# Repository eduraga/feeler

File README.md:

# Feeler

## Installation

- Install MindsetProcessing http://jorgecardoso.eu/processing/MindSetProcessing/ in Processing.
- Install feelerSerial in Processing.

### Without PHP backend
- Change the first in feelerApp.pde line to ```boolean debug = true;```.
- The application now runs in 'debug' mode, so you can login by clicking 'L' on the keyboard.

### With PHP backend
- Install a PHP server, such as MAMP https://www.mamp.info/en/, and run it.
- Install the contents of /SimpleUsers (a modified version of: https://github.com/Repox/SimpleUsers and create a user).
  - Edit the configuration file, located at simpleusers/config.inc.php, then run the install script which is located at simpleusers/install.php As an alternative to the install script, edit the configuration file. The tables can be created manually, by opening tables.sql and pasting the tables into phpMyAdmin.
- Edit feelerApp/data/config.json to reflect your environment.

## Running
- Run feelerApp.pde (in /feelerSerial) and try to create a user or log in (or ref. to running without PHP).
- Set ```simulateMindSet``` to true to test without MindWave.
- Set ```simulateBoxes``` to true to test without the boxes.
- Change ```countDownStartMeditate``` and ```countDownStartStudy``` (in minutes, accepts fractions) to the appropriate values.

## License
Feeler is licensed under GPL3 license, see COPYING

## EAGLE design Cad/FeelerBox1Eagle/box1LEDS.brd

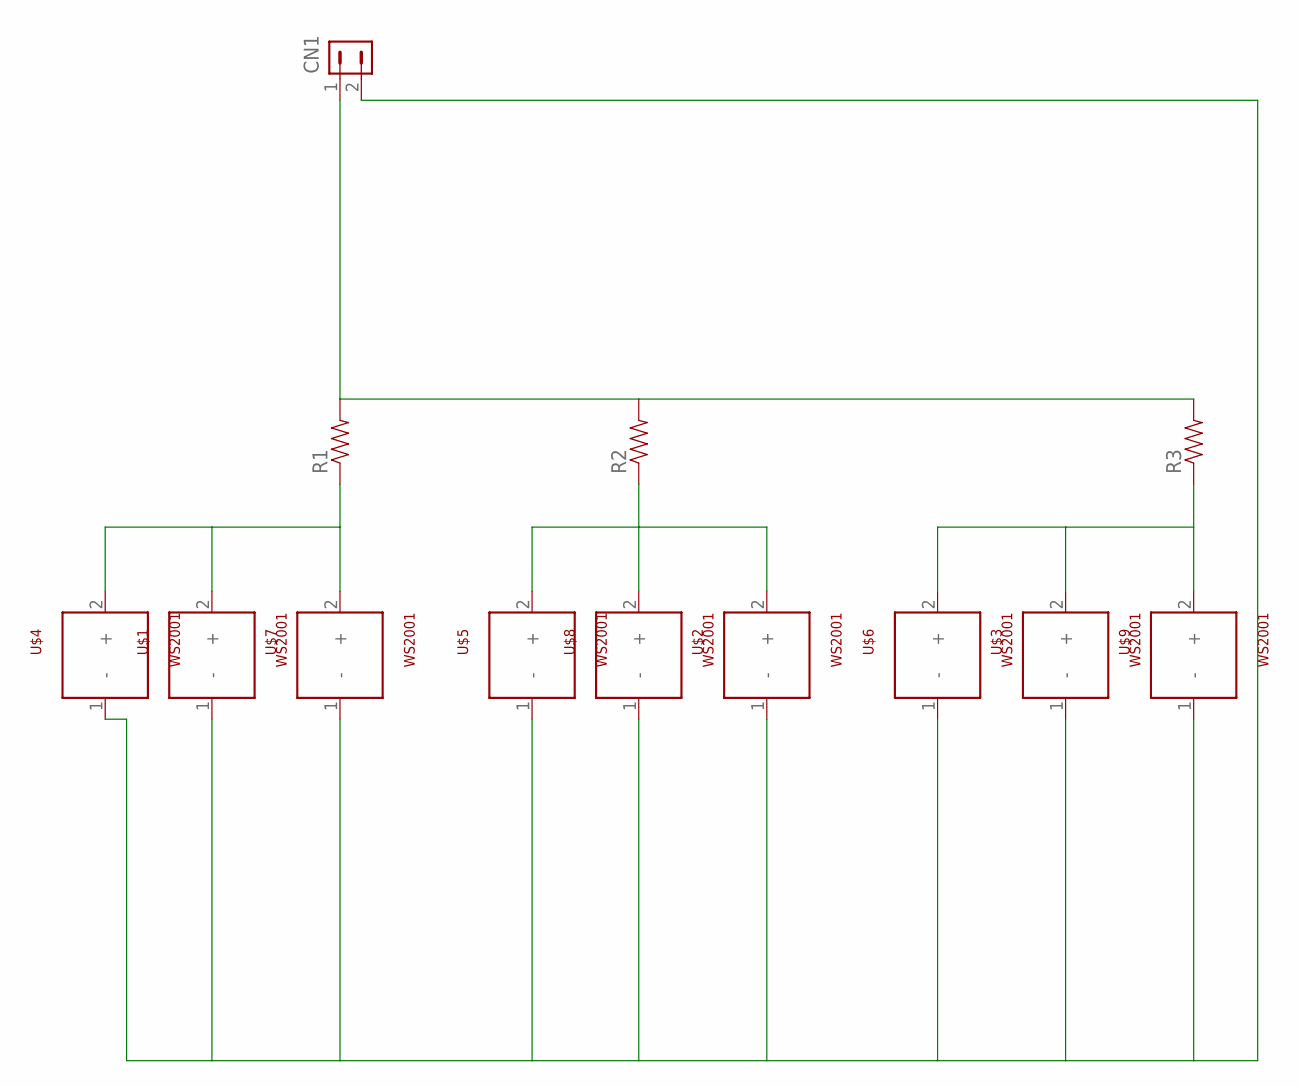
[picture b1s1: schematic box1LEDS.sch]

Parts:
CN1: HDR-1X2-SIP-100; SIP-100-2V
R1, R2, R3: RESISTORPTH-1/4W; AXIAL-0.4
U$1, U$2, U$3, U$4, U$5, U$6, U$7, U$8, U$9: WS2001; WH2001

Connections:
GND: CN1.2, U$1.1 (-), U$2.1 (-), U$3.1 (-), U$4.1 (-), U$5.1 (-), U$6.1 (-), U$7.1 (-), U$8.1 (-), U$9.1 (-)
unnamed: R3.P$1 (1), U$3.2 (+), U$6.2 (+), U$9.2 (+)
unnamed: R2.P$1 (1), U$2.2 (+), U$5.2 (+), U$8.2 (+)
unnamed: R1.P$1 (1), U$1.2 (+), U$4.2 (+), U$7.2 (+)
unnamed: CN1.1, R1.P$2 (2), R2.P$2 (2), R3.P$2 (2)

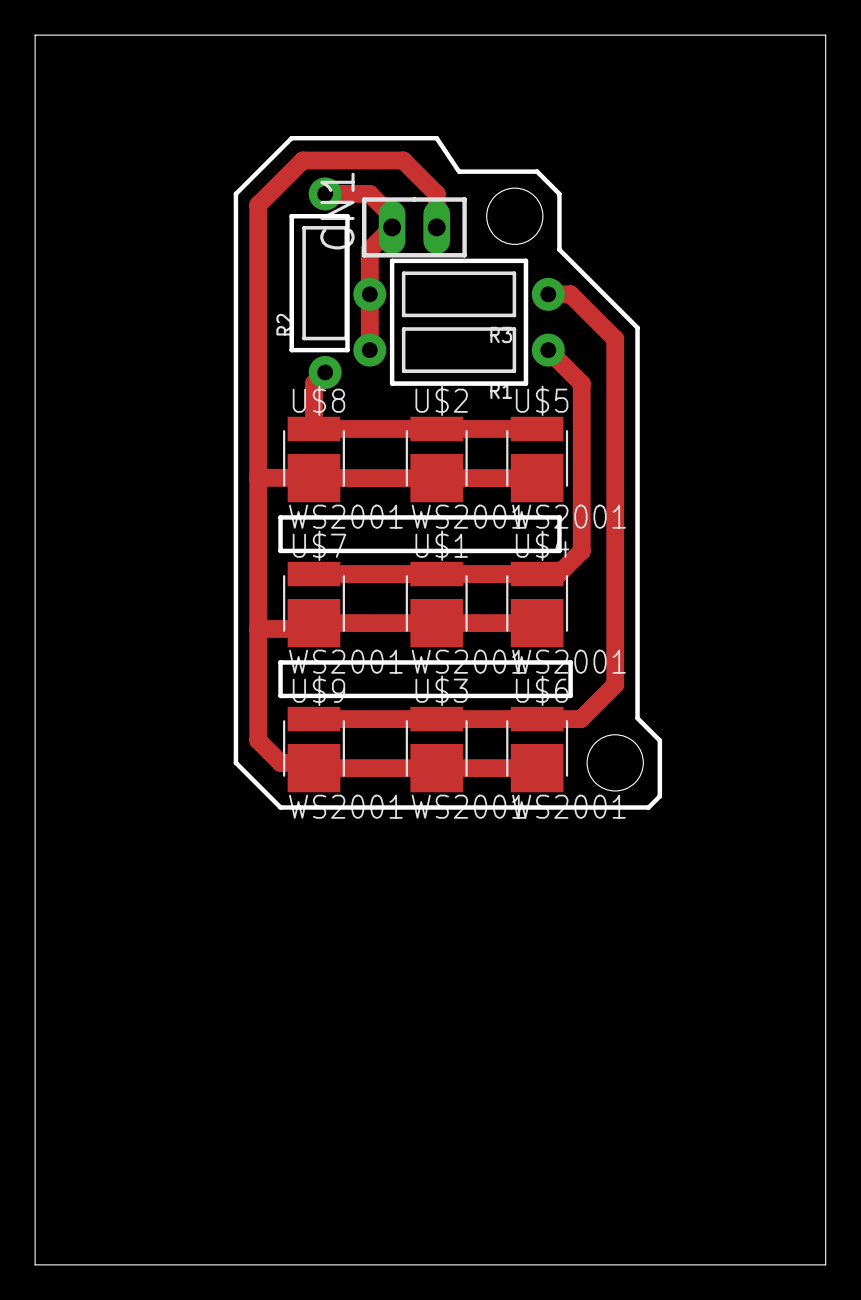
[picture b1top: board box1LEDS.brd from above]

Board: 2 copper layers, 44.7 x 69.7 mm, 13 parts (0 on the bottom side), 5 nets.

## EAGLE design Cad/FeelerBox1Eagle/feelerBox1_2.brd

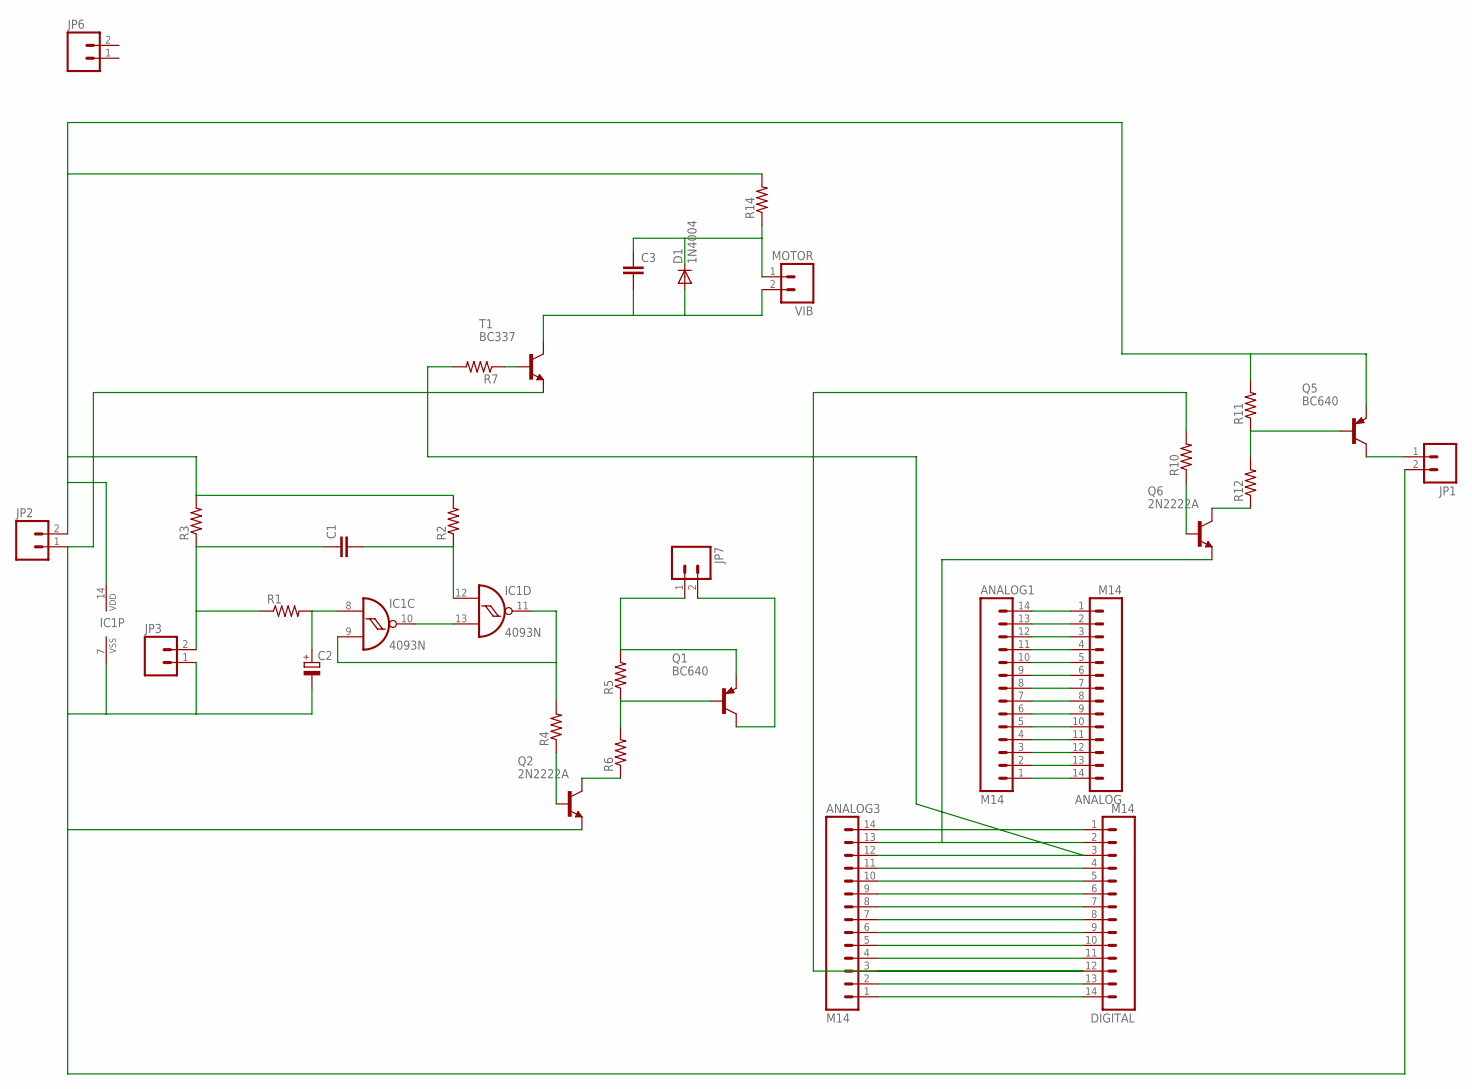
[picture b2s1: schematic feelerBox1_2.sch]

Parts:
ANALOG, ANALOG1, ANALOG3: M14; 1X14
C1: 0.1UF-50V-20%(PTH)KIT-EZ; CAP-PTH-SMALL-KIT
C2: CPOL-EUE2.5-5; E2,5-5
C3: CAPKIT; CAP-PTH-SMALL-KIT
D1: 1N4004; DO41-10
DIGITAL: M14; 1X14
IC1: 4093N; DIL14
JP1, JP2, JP3, JP6, JP7: M02PTH; 1X02
Q1, Q5: BC640; TO92-BCE
Q2, Q6: 2N2222A; TO18
R1, R2, R3, R7: RESISTORAXIAL-0.3; AXIAL-0.3
R4, R5, R6, R10, R11, R12, R14: RESISTORPTH-1/4W-VERT; AXIAL-0.1
T1: BC337; TO92
VIB: MOTOR; 1X02

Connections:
A1: IC1.9 (I1), IC1.11 (O), R4.P$2 (2)
A2: ANALOG.9, ANALOG1.6
A3: ANALOG.10, ANALOG1.5
A4: ANALOG.11, ANALOG1.4
A5: ANALOG.12, ANALOG1.3
A6: ANALOG.13, ANALOG1.2
A7: ANALOG.14, ANALOG1.1
A8: ANALOG3.4, DIGITAL.11
A9: ANALOG3.3, DIGITAL.12, R10.P$2 (2)
BATTERYGND: C2.-, IC1.7 (VSS), JP1.2, JP2.1, JP3.1, Q2.1 (E), T1.1 (E)
BATTERYPWR: IC1.14 (VDD), JP2.2, Q5.E, R2.P$2 (2), R3.P$2 (2), R11.P$2 (2), R14.P$2 (2)
D2: ANALOG3.12, DIGITAL.3, R7.P$2 (2)
D4: ANALOG3.10, DIGITAL.5
D6: ANALOG3.8, DIGITAL.7
D7: ANALOG3.7, DIGITAL.8
D8: ANALOG3.6, DIGITAL.9
D9: ANALOG3.5, DIGITAL.10
GND: ANALOG3.13, DIGITAL.2, Q6.1 (E)
GND2: ANALOG3.14, DIGITAL.1
unnamed: IC1.10 (O), IC1.13 (I1)
unnamed: Q1.B, R5.P$1 (1), R6.P$2 (2)
unnamed: C2.+, IC1.8 (I0), R1.P$2 (2)
unnamed: ANALOG.6, ANALOG1.9
unnamed: C1.1, JP3.2, R1.P$1 (1), R3.P$1 (1)
unnamed: C1.2, IC1.12 (I0), R2.P$1 (1)
unnamed: Q2.3 (C), R6.P$1 (1)
unnamed: JP7.2, Q1.C
unnamed: Q2.2 (B), R4.P$1 (1)
unnamed: JP7.1, Q1.E, R5.P$2 (2)
unnamed: ANALOG.1, ANALOG1.14
unnamed: ANALOG.2, ANALOG1.13
unnamed: ANALOG.3, ANALOG1.12
unnamed: ANALOG.4, ANALOG1.11
unnamed: ANALOG.5, ANALOG1.10
unnamed: R7.P$1 (1), T1.2 (B)
unnamed: ANALOG.7, ANALOG1.8
unnamed: ANALOG.8, ANALOG1.7
unnamed: Q5.B, R11.P$1 (1), R12.P$2 (2)
unnamed: ANALOG3.1, DIGITAL.14
unnamed: ANALOG3.2, DIGITAL.13
unnamed: ANALOG3.9, DIGITAL.6
unnamed: ANALOG3.11, DIGITAL.4
unnamed: Q6.3 (C), R12.P$1 (1)
unnamed: C3.2, D1.A, T1.3 (C), VIB.2
unnamed: C3.1, D1.C, R14.P$1 (1), VIB.1
unnamed: Q6.2 (B), R10.P$1 (1)
unnamed: JP1.1, Q5.C

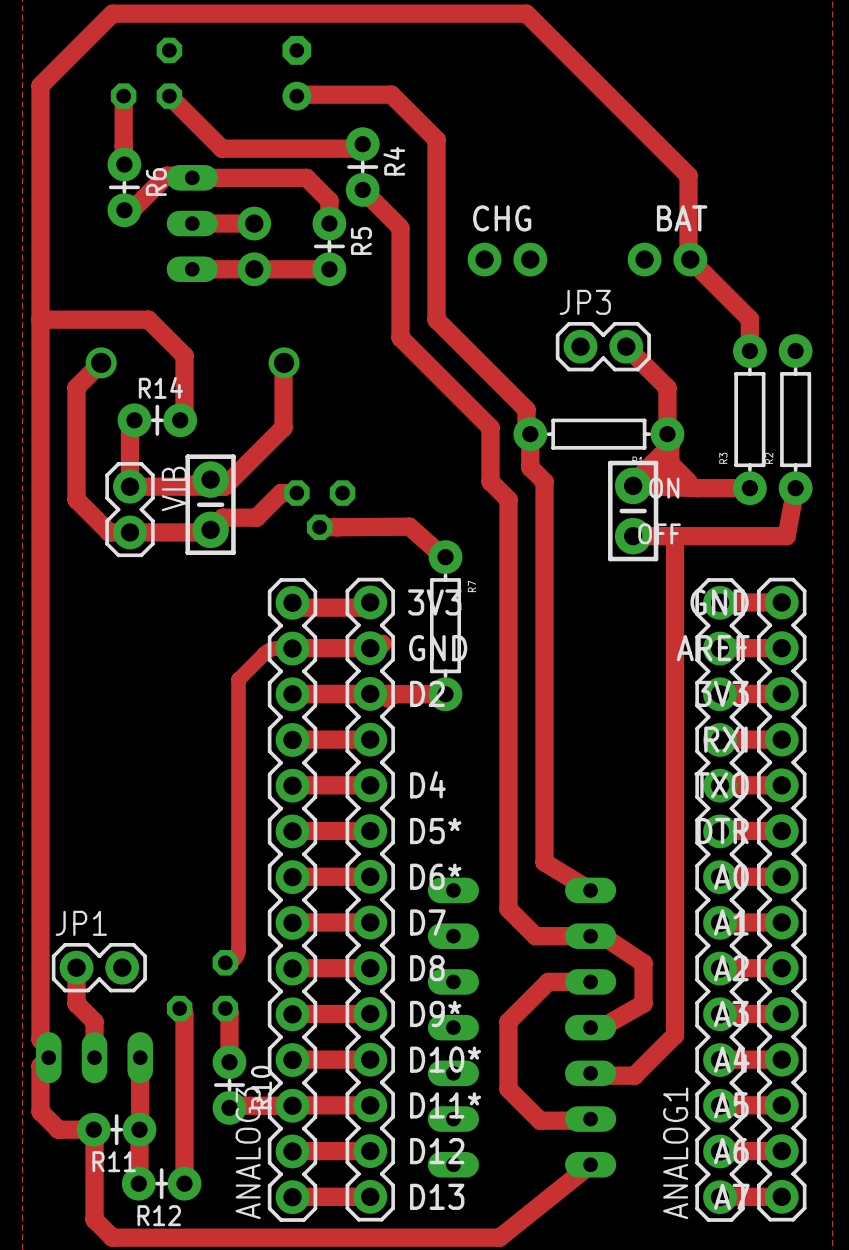
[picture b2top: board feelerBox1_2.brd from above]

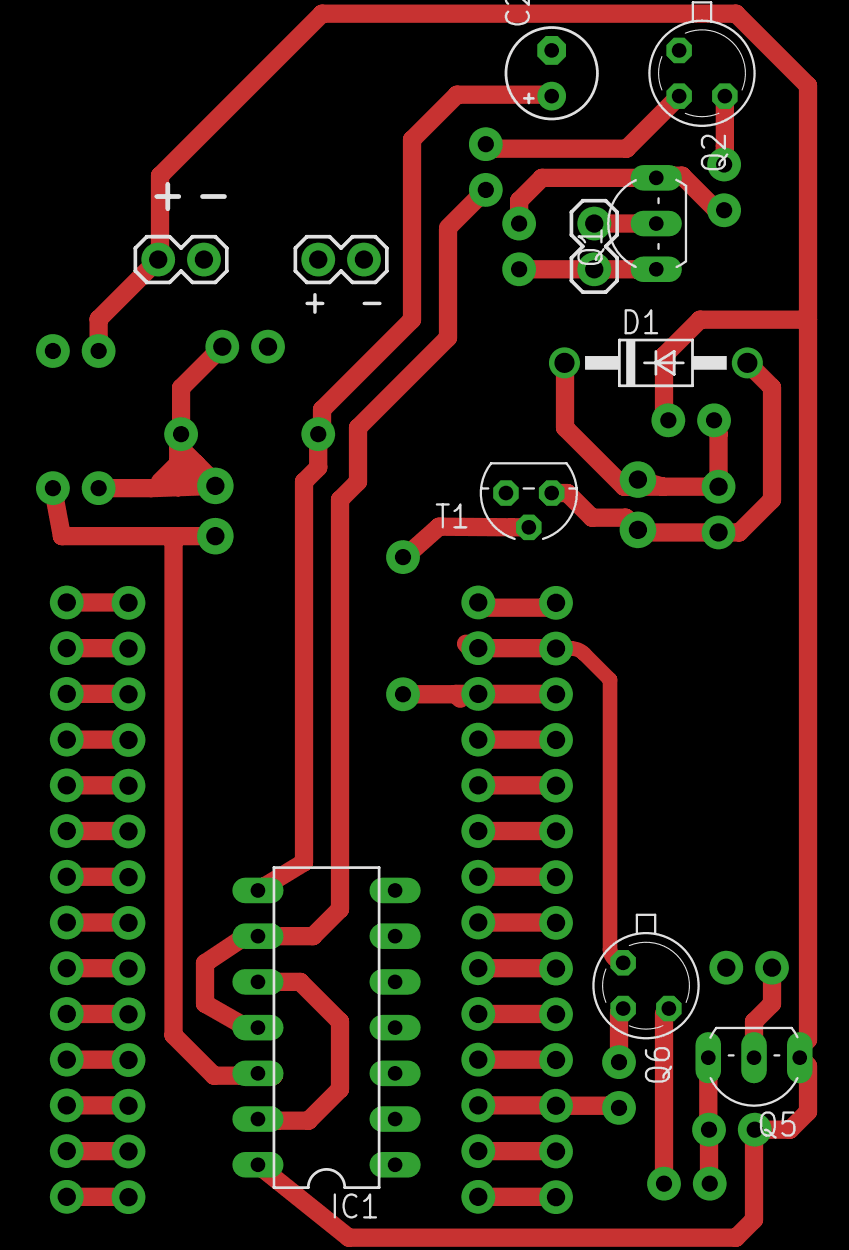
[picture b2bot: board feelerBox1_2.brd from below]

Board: 2 copper layers, 31 parts (11 on the bottom side), 47 nets.

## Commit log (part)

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2016-01-20 Updated readme.md with todo list
2016-01-25 Created basic user management with php.
2016-01-28 feelerSerial0.001 uploaded
    first version, arduino code coming soon
2016-01-28 readMe fix
2016-01-29 typo :D
2016-01-29 another typo
2016-01-29 Merge remote-tracking branch 'origin/master'
    # Conflicts:
    # feelerSerial/README.md
2016-01-29 Made something a bit more clear
2016-01-29 Feeler Arduino serial library
2016-01-29 autoformat
    re-indent
2016-02-02 Added FloatTable to load csv files and "start a session" tab.
2016-02-02 Added screen capture. Triggered by 'c' key when in debug mode.
2016-02-02 Now loading user data from user folder.
2016-02-07 Updates to optimize for the bluetooth connections
    Serial packet buffer changed. Works better with bluetooth
2016-02-08 Simplified some things
2016-02-16 Added visualisation and a bunch of todos. Updated read me.
2016-02-18 Created basic visualisation of averages for (10) last sessions.
    Also added a check to FloatTable to check if the row is not empty.
    Updated read me file.
2016-02-19 Improved basic averages visualisation.
2016-02-19 Added support for file choosing via graph.
    Still a bit buggy.
2016-02-25 Made overallAvgs graph reusable for reg and self-assessment.
2016-02-25 Created call for session activity upon click on session EEG graph.
2016-02-25 Converted overallAvgs to class so it's more flexible.
2016-02-25 Made LineChart (was avgGraph) into a class for reusability.
2016-02-25 Added real values to line chart in a session.
2016-02-25 Added background color for graph based on the progress phase.
2016-02-29 Added scroll container to home page.
2016-02-29 Added navigation to/from home page and graphic elements to small boxes.
2016-02-29 Put background back to line chart.
2016-03-10 Fixed lack-of-data bug.
2016-03-10 Added start session button and some content. Fixed logout issue (unable to login after logging out).
2016-04-12 Added communication with MindSet device.
2016-04-12 Now saving brain log to correct folder, inside user-data/[username]
2016-04-12 Added flush() and close() to finish saving mind file.
2016-04-12 Fixed labels for LineChart.
2016-04-13 Fixed labels.
2016-04-13 Added call to loadFiles() after assessment is done.
2016-04-13 Check if file has extension .tsv before loading.
2016-04-13 Put assessment files in their own folder.
2016-04-13 Added personal experience placeholder page.
2016-04-13 Reset new session after saving assessment.
2016-04-14 Fixed eegAct data loading on mouse click.
2016-04-14 Made visualisation size dynamic.
2016-04-14 Fixed some function names.
2016-04-17 Changed folder structure to accomodate screenshots.
2016-04-18 Added screenshot for on new session page.
2016-04-19 Put screenshot threasholds in a separate function.
2016-04-19 Now loading also first row of data.
2016-04-22 Centered graph. Fixed bugs for when there is no user data.
2016-04-22 Removed null folder creation.
2016-04-22 Loading screenshots based on their time code.
    This needs to be checked for accuracy.
2016-04-23 Removed tab.
2016-04-23 App now detects screen resolution and fills the whole space. Full screen is also available.
2016-04-23 Added basic visual clue for mouse over.
2016-04-24 Added mouse over functionality.
2016-04-24 Added average assessments to assessment page. Fixed session dates.
2016-04-24 Added creation of "user-data" folder case it doesn't exist.
2016-04-24 Added export session brain data raw file.
2016-04-24 Eagle drawings for box1
2016-04-26 fixes
    Fixes, and made made box1Ledboard smaller to improve wifi signal
2016-04-26 box1led milling file update
2016-06-03 Fixed mouse over problem (issue #22 )
2016-06-03 Partially fixed issue #24 (now app doesn't break)
2016-06-03 Removed link from logo (issue #25)
2016-06-03 Export also assessment data (issue #23)
2016-06-08 Check if Mindwave is connected before displaying "start session" button.
2016-06-08 Check if Mindwave is connected, then show step 2 (connect the boxes).
2016-06-09 Update interaction_boxes
2016-06-09 Added pause/resume to counter.
2016-06-10 Added countdown to study phase. Added play/pause button to countdown. Issue #32.
2016-06-11 Made attention/meditation levels visible on main chart.
2016-06-11 Created simple radio button for feeling assessment.
2016-06-11 Saving assessment feelings.
2016-06-11 Hid playPauseBt when counter is stopped.
2016-06-11 Added page 2/3 of assessment (relaxation)
2016-06-11 Added page 3/3 of assessment (attention)
2016-06-11 Added line chart to session assessment (issue #43).
2016-06-22 Added "play" session. Removed recording from assessment session (issue #47)
2016-06-22 Indicated that there is a screenshot with a rectangle at the bottom of the graph (issue #52 ).
    This needs to be made more efficient in the future.
2016-06-22 Fixed loading bug for when there's no data (part of issue #46).
2016-06-27 Added "previous" buttons to assessment (issue #38).
2016-06-29 Redirected user to session data after responding assessment (issue #9)
2016-06-29 Fixed graph phases (meditate, study, play) style.
2016-07-07 Added mouse over thumbnail back.
2016-07-07 Fixed z-index of image thumbnail. Fixed first element in line chart.
2016-07-20 Added feeler serial example to data folder.
2016-08-04 example update
    1
2016-08-04 baahaaaaa
2016-08-04 Implemented serial library.
2016-08-05 feelerSerial, update to time-out when serial not received/sent
2016-08-06 Implemented support for boxes. Added count up for game. Changed start time for counter in meditate and study ( #65 ). Changed home screen.
2016-08-06 Set record button to appear only after connections have been established ( #30 )
2016-08-06 Added back att an rlx to mouse over #51
2016-08-06 Limited mouse over to visualisation area.
2016-08-06 Added button to go back to current session home.
2016-08-06 Added "window" (modal) to open bigger screenshots. Fixed bug when exiting without mindset.
2016-08-06 Fixed bug in modal.
2016-08-06 Clean up survey buttons when clicking in overall.
2016-08-07 Fixed line chart ranges.
2016-08-07 Fixed bug with eegAct values.
2016-08-07 Removed negative values for bar charts.
2016-08-08 Updated readme.
2016-08-08 Fixed redirection to overall page when finished with survey.
2016-08-08 Zeroed assessment replies. Removed "play" from chart since it's not being recorded.
2016-08-09 Fixed led states. Updated readme.
2016-08-10 font
2016-08-10 Fixed style bugs.
2016-08-11 Personal experience and heading position
2016-08-15 Layout Assess sections
    Layout sliding bars and buttons + answers saved page
2016-08-16 Layout review pages
2016-08-19 layout of login, sliders, averages active area
2016-08-19 img home
2016-08-26 layout home
2016-08-29 Layout login button home, layout screenshot EEG
2016-08-29 Feeler home image
2016-08-31 Fixed range in line chart mouse over ( #88 )
2016-08-31 Fixed login issue ( #99 )
2016-08-31 Added log in back to debug mode.
2016-08-31 Display status of boxes and MindWave ( #97 )
2016-09-01 Fixed timeline display.
2016-09-01 Fixed ranges also for visualisation scale (0%—100%)
2016-09-01 Fixed modal bug ( #72 )
2016-09-02 Fixed out of range averages ( #100 )
2016-09-07 Added debug for box led state. Changed meditation and attention thresholds.
2016-09-17 just a couple of comments, & starting my branch
2016-09-18 measured timing problems in current file output system and started building a queued+threaded logging system
2016-09-18 still working in async file output
2016-09-18 still trying to figure out the async mechanism
2016-09-19 created a minimum threaded log system
2016-09-19 achieved millisecond perfect precision in log. There is still an unknown problem with the file writing
2016-09-19 failed attempt to child the fileprint thread to the logging thread
2016-09-19 achieved async file writing as child of threaded logging :)
2016-09-21 Fixed 'hiccup' with pAttention
2016-09-21 Fixed "study" and "play" label orders ( #102 ).
    Actually put a condition to not show it case some data is corrupted.
2016-09-21 Trying to address missing data ( #101 ).
2016-09-21 so far failed attempt to integrate async logging to the app
2016-09-21 Created the experimental branch. The logging thread will run in parallell until finished
2016-09-22 half way integrated but for some reason the logger thread can't start paused and then restart. it can log from the beginning of the app load. in the test environmet it is capable of pausing albeit I 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
2016-09-23 figured out a way of starting the logger in pause. Will require implementation of atomic boolean
2016-09-23 implemented solution works in the experimental environment. about to integrate
2016-09-23 implemented threaded logging is working in the context of feeler app. now we need to log the actual data in the alternate logging system
2016-09-23 evaluated the time evenness of the test run
2016-09-23 implemented change the writer file in runtime
2016-09-23 trying to coordinate file and screenshot naming.
2016-09-24 design idea for central filename administration object
2016-09-24 forward with the filenamemanager
2016-09-26 blind inclusion of the mindwave library as part of the logging thread, instead of the main thread
2016-09-27 created a filenamemanager in isolation
2016-09-27 created file listing ability to enable screenshot list
2016-09-27 integrated loaDir filenamemanager in loadfiles tab
2016-09-28 more and more problems with filename management
2016-09-28 new branch. because the changes in file names management would take very long
2016-09-29 synchronisation issues with the boxes
    Adding Niklas changes to synchronising the app with the boxes
2016-09-30 created an isolated mindset for better testing
2016-09-30 fix graph in mindsetalone
2016-09-30 isolated mindset reader ready
2016-09-30 mindset alone graph as a class and discovered sampling rate of all datasets.
2016-09-30 new logic of integration of the mindset logging to try
2016-09-30 eeg events were not actually passed to thread. fixed and found more problems.
2016-09-30 started application of the new idea. not functional yet
2016-09-30 included snippets from no-filenamemanager branch
2016-09-30 implementation ready for test
2016-10-03 better,simpler approach of async integration attempt 3
2016-10-03 fetched fixed line graph file
2016-10-03 fixed infinite loop in graphing function when the log is shorter than 100 lines.
2016-10-03 thread("_screenshot") didnt work. trying fixes in lineGraph
2016-10-03 screenshots now in their right place. There still is a problem of screenshot overlapping
2016-10-05 solved problem where the logger still records eeg data while the user is answering the poll. #108
2016-10-06 mini tool for comparisong of different data logs #108
2016-10-06 solved the problem with the amount of labels. Now the amount is chosen in a line of code regardless of the dataset #108
2016-10-08 force restart timer on new session, for issue #108
2016-10-09 Create COPYING
2016-10-10 #109 assessment survey fix, first try
2016-10-10 #108 fix for logger measuring time while session was stopped, making time to start from >0 on retake. logger.pause() on stop will set active flag to false, therefore timer will restart on start.
2016-10-10 #108 fixed timer would restart on each phase and not log play. fixed mispelled variable name
2016-10-10 fixed problem where the screenshot rectangles could get too small
2016-10-10 first attempt to address #110
2016-10-10 #110 solved, but testing is still minimum
2016-10-12 Patched two button display problems #96 and #93
2016-10-13 #113 correction
2016-10-13 #112 hid problematic pause button and other try block where hanging was suspected to happen
2016-10-18 test push for connect to boxes only once next screen was drawn
2016-10-18 forgot to save a file
2016-10-18 Feeler app - boxes synchronized
2016-10-19 niklas lines to sync boxes better
2016-10-19 applied niklas tweak for boxes in the code
2016-10-19 added niklas box sync fix
2016-10-19 attempt preventing box bluetooth serial to try connection when they are already connected.
2016-10-19 added pendant note
2016-10-27 new session button
2016-11-01 Layout changes

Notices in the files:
parts and their libraries:
SparkFun-Passives: Licensing: Creative Commons ShareAlike 4.0 International - https://creativecommons.org/licenses/by-sa/4.0
con-hdrs40: Copyright (C) 2004, Bob Starr (bobstarr@mindspring.com)
